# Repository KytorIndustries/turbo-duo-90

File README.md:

# Turbo Duo DIN 8 90 Degree
The PC Engine Duo / Turbo Duo DIN 8 AV port protrudes out the side, an inconvenience in some setups. This two piece PCB assembly is designed to rotate the DIN 8 connector 90 degrees to face towards the rear. The two pieces consist of the upper (3E-300011) and base (3E-300012).

The Turbo Duo uses a full-size DIN 5 connector, which if modded for RGB video one typically chooses a DIN 8 270 connector for consistency with the Duo R and readily available AV cables. Unfortunately PCB 180 mount DIN 8 270 male connectors are unavailable at this time, so this board is designed to accept both DIN 8 262 and 270 male connectors.

The only possibility at the time of this writing is to use DIN 8 262 male connectors which are technically incompatible with DIN 8 270 female, although if you bend the pins you can force it to work (functional, but not recommended). Therefore if using this device I would recommend replacing the PCB 90 mount DIN 8 270 female connector on your Turbo Tuo with a DIN 8 262 female connector.

The lower board includes an optional sync stripper for CSYNC output.

A provision is provided for mounting to a plastic enclosure shell. A shell has not been designed as part of this project.

## Files Included
- **PCB Design Files** (KiCAD, Gerber)
- **Bill of Materials** (XLSX)
- **CAD** (STEP)
- **Photos**

## Assembly
1. Solder all components in place. Alternatively, if a sync stripper is not desired do not populate C1-2, SW1 or U1 and solder jumper JP1.
2. Solder upper board to lower board.

## PCB Revision History
- Rev 1 - Initial release
- Rev 0 - Development (unreleased)

## License
This project is open-source under the [CC BY 4.0 (Attribution 4.0 International)](https://creativecommons.org/licenses/by/4.0/).

## Disclaimer
This project is provided "as-is" without any warranty, express or implied, including but not limited to warranties of merchantability or fitness for a particular purpose. No support is provided.

Amazon links are affiliates.

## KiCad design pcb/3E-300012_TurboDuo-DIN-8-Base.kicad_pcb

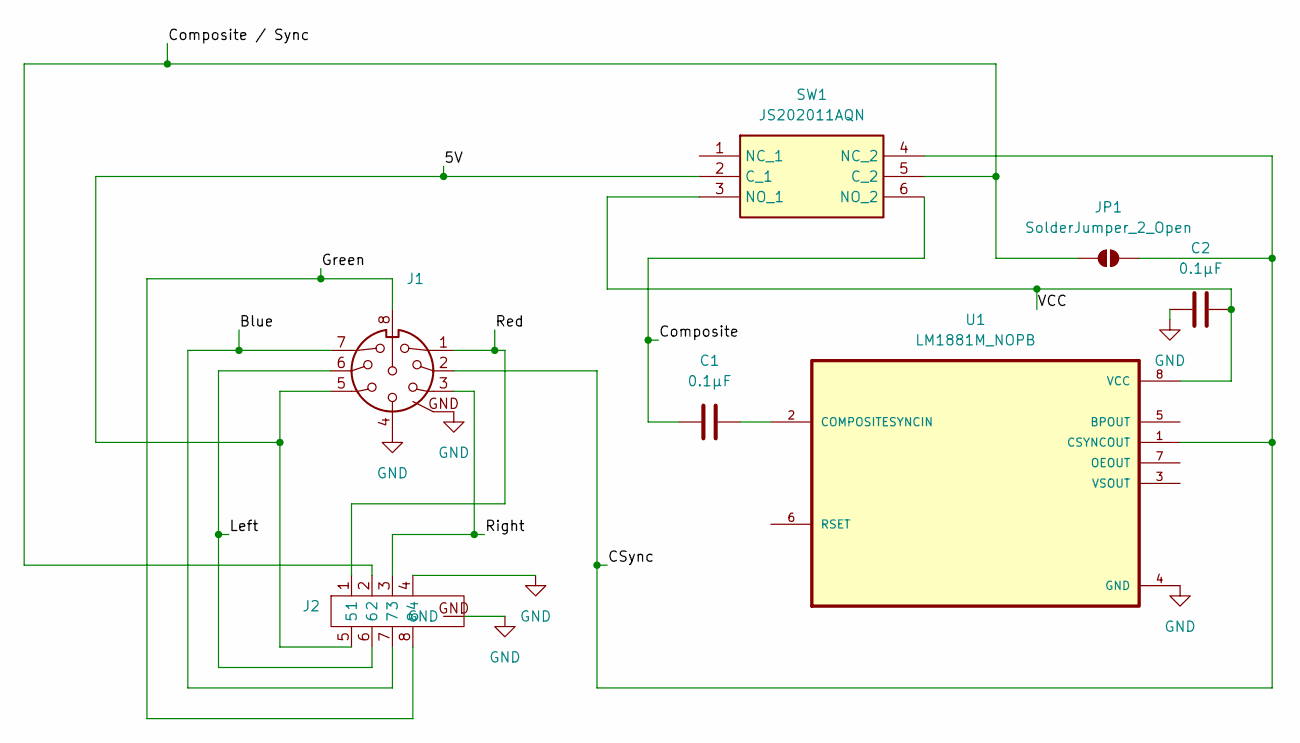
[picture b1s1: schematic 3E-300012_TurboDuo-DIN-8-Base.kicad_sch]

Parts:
C1, C2: 0.1µF; C_0805_2012Metric_Pad1.18x1.45mm_HandSolder
J1: DIN_8_270_Female_(90)
J2: Tee Joint 9 Pin Plane
JP1: SolderJumper_2_Open; Jumper Small (1.5x1mm)
SW1: JS202011AQN; Mouser Part Number 611-JS202011AQN
U1: LM1881M_NOPB; LM1881M

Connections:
/5V: J1.5, J2.5, SW1.2 (C_1)
/Blue: J1.7, J2.7
/CSync: J1.2, JP1.2 (B), SW1.4 (NC_2), U1.1 (CSYNCOUT)
/Composite: C1.1, SW1.6 (NO_2)
/Composite / Sync: J2.2, JP1.1 (A), SW1.5 (C_2)
/Green: J1.8, J2.8
/Left: J1.6, J2.6
/Red: J1.1, J2.1
/Right: J1.3, J2.3
/VCC: C2.2, SW1.3 (NO_1), U1.8 (VCC)
GND: C2.1, J1.4, J1.GND, J2.4, J2.GND, U1.4 (GND)
unnamed: C1.2, U1.2 (COMPOSITESYNCIN)

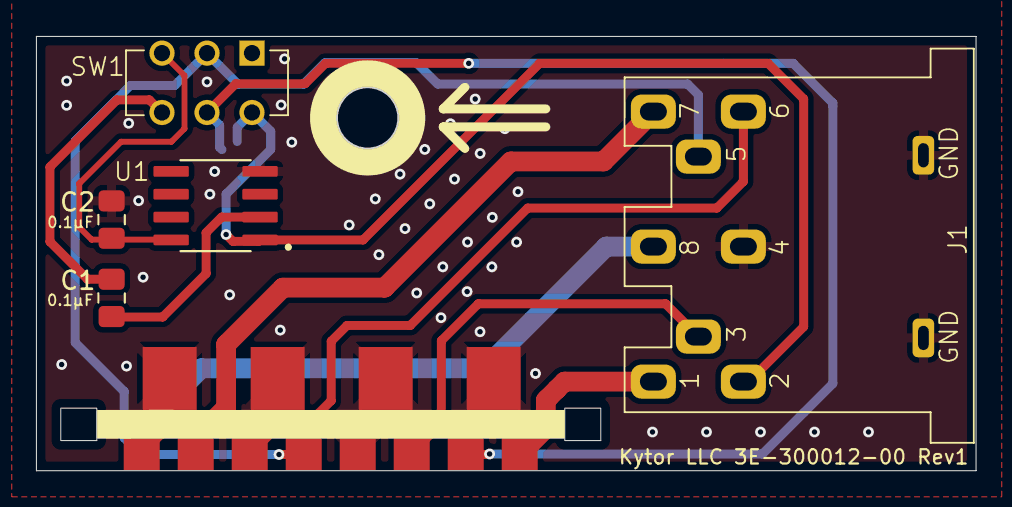
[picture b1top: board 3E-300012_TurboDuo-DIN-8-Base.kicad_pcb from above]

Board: 2 copper layers, 52.1 x 24.1 mm, 7 parts (1 on the bottom side), 12 nets.

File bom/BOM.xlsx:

Name | Manufacturer | Quantity | Value | Pattern | RefDes | Procurement
Female 90 DIN 8 270 | RTLECS | 1 |  | DS-8-101-270 | J1 | https://www.aliexpress.us/item/3256802145433954.html
Male 180 DIN 8 262 | RTLECS | 1 |  | DIN 8 262 180 | J2 | https://www.aliexpress.us/item/3256801687296911.html
 | Various | 2 | 100nF | 805 | C1-2 | https://www.mouser.com/ProductDetail/Samsung-Electro-Mechani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
 | C&K | 1 |  | JS202011AQN | SW1 | https://www.mouser.com/ProductDetail/CK/JS202011AQN?qs=LgMIj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
 | Texas Instruments | 1 |  | SOIC-8 | U1 | https://www.mouser.com/ProductDetail/Texas-Instruments/LM188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

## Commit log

2025-05-04 Initial Upload
2025-05-05 Corrections
2025-05-05 Embedded Models
    KiCAD PCB Layout files now include embedded STEP files for components.
